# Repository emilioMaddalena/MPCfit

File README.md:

# MPCfit

Lightweight MPC approximations through tailored neural networks.

## Description :books:

We propose a particular feedforward neural network architecture to approximate model predictive controllers from data. The network features a quadratic program as one of its internal layers, employed to learn the MPC dual, as well as a final projection layer to guarantee feasibility of the control actions. It is shown that, given an appropriate network size, **any linear MPC controller can be learned**.

The so-called piecewise-affine neural network (PWA-NN) was used to learn an MPC controller for a buck dc-dc converter, and then embedded on an STM32 microcontroller. The control computations were carried out periodically in **less than 30 microseconds**. This repository contains all the files related to the project.

Evolution across epochs:

Final results:

## References :books:

```
@article{maddalena2021embedded,
  title={Embedded PWM predictive control of DC-DC power converters via piecewise-affine neural networks},
  author={Maddalena, E. T. and Specq, M. W. F. and Wisniewski, V. L. and Jones, C. N.},
  journal={IEEE Open Journal of the Industrial Electronics Society},
  volume={2},
  pages={199--206},
  year={2021},
  publisher={IEEE}
}
```
```
@article{maddalena2020neural,
  title={A neural network architecture to learn explicit MPC controllers from data},
  author={Maddalena, E. T. and Moraes, C. G. da S. and Waltrich, G. and Jones, C. N.},
  journal={IFAC-PapersOnLine},
  volume={53},
  number={2},
  pages={11362--11367},
  year={2020},
  publisher={Elsevier}
}
```

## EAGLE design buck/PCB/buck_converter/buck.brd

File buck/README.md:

## Buck converter 

A schemtic of the dc-dc converter: 

## Folders

:open_file_folder: Documents: PDF documents relevant to the project.

:open_file_folder: Firmware: C code for the STM32L4 microcontroller. The projects were developed in the STM32 CUBE-IDE and CUBE-MX environments.

:open_file_folder: PWA-NN: Contains the MATLAB scripts where the system model is defined and the MPC controller is designed and sampled. Also contain the python code used for defining and training the PWA-NN.

:open_file_folder: PCB: The schematic, layout and gerber files for the buck dc-dc converter printed circuit board. The design was carried out in Autodesk Eagle 9.5.

:open_file_folder: Scope: A set of oscilloscope screenshots obtained during operation (refer to the paper), and their associated .csv files.

:open_file_folder: Sketch: Illustration files for each of the figures present in the paper. Drawn in Sketch 68.2.

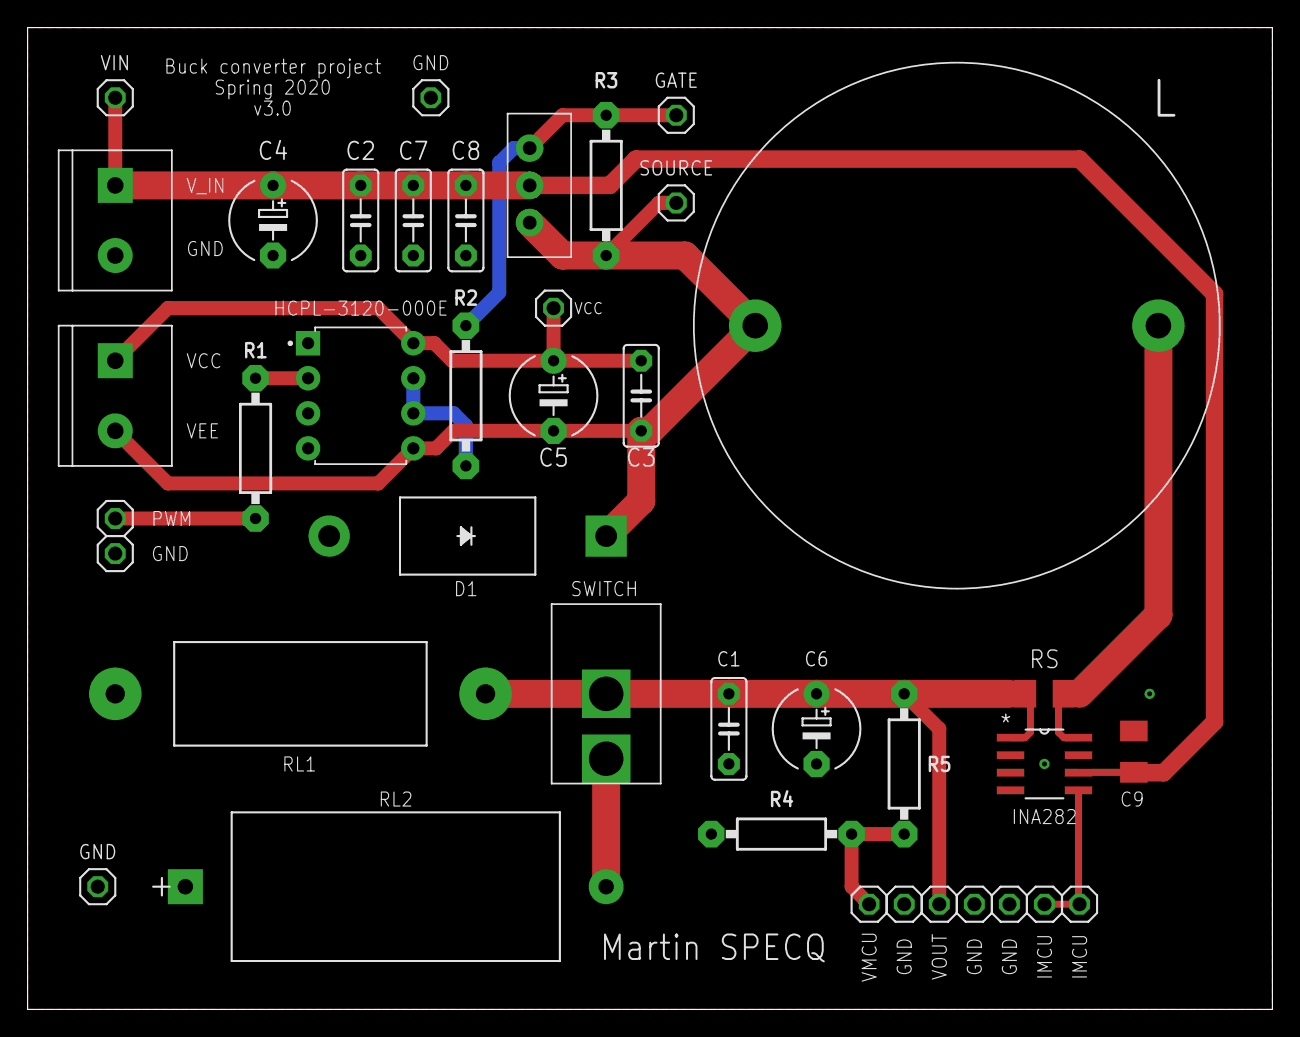
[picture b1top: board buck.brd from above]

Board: 2 copper layers, 90.2 x 71.1 mm, 40 parts (0 on the bottom side), 13 nets.

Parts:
C1, C2, C3: 100n; C5B2.5
C4, C5: 100u; E5-6
C6: 56u; E5-6
C7: 10n; C5B2.5
C8: 1n; C5B2.5
C9: 100n; C1206K
D1: DIODE_DO-201AD
GATE: 1X01
GDRVR: TE_282837-2
GND, GND2: 1X01
L: 10m; INDRD2921W163D3810H2616P
R1: 1k; 0207/10C
R2: 100; 0207/10C
R3: 10k; 0207/10C
R4: 22k; 0207/10C
R5: 56k; 0207/10C
R7, R9, R10, R11, R12, R13, R14, R15: 1X01
RL1: 100; RES_AC05
RL2: 100; YAG_SQP500
RS: 150m; M1206
SOURCE: 1X01
T: MOSFETMOSFET; MOSFET
U1: HCPL-3120-000E; DIP762W65P254L990H470Q8
U2: INA282AID; D8
U$1: ON_OFF
VCC: 1X01
VIN: 1X01
VMCU: 1X01
V_IN: TE_282837-2

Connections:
G: GATE.1, R2.2, R3.2, T.G
GND: C1.2, C2.2, C4.-, C6.-, C7.2, C8.2, C9.2, D1.2, GND.1, GND2.1, R4.1, R10.1, R11.1, R12.1, R13.1, RL1.1, RL2.1, U1.3, U2.2, U2.3, U2.7, V_IN.2
IMCU: R14.1, R15.1, U2.5
IND: L.2, RS.2, U2.8
unnamed: R2.1, U1.6, U1.7
unnamed: R1.2, U1.2
unnamed: RL2.2, U$1.P$2
PWM: R1.1, R9.1
VCC: C3.1, C5.+, GDRVR.1, U1.8, VCC.1
VEE: C3.2, C5.-, D1.1, GDRVR.2, L.1, R3.1, SOURCE.1, T.S, U1.5
VIN: C2.1, C4.+, C7.1, C8.1, C9.1, T.D, U2.6, VIN.1, V_IN.1
VMCU: R4.2, R5.1, VMCU.1
VOUT: C1.1, C6.+, R5.2, R7.1, RL1.2, RS.1, U2.1, U$1.P$1

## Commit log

2020-12-13 First update
2020-12-13 Picture update
2020-12-13 Update picture
2021-06-17 include all files
2021-06-17 create more readmes
2021-06-17 add buck diagram
2021-06-17 upload new documents
2021-06-17 update matlab scripts
2021-06-17 add gif
2021-06-17 relocate figs
2021-06-17 update python scripts
2021-06-17 organize python code and folder
2021-06-17 create new readme
2021-06-18 reorganize project
2021-06-18 add buck photo
2021-06-18 update python files
2021-06-18 rename folders
2021-06-18 clean pcb folder
2022-06-22 Bump numpy from 1.20.3 to 1.22.0 in /files/code/python
    Bumps [numpy](https://github.com/numpy/numpy) from 1.20.3 to 1.22.0.
    - [Release notes](https://github.com/numpy/numpy/releases)
    - [Changelog](https://github.com/numpy/numpy/blob/main/doc/HOWTO_RELEASE.rst)
    - [Commits](https://github.com/numpy/numpy/compare/v1.20.3...v1.22.0)
    ---
    updated-dependencies:
2023-07-06 Bump scipy from 1.6.3 to 1.10.0 in /files/code/python
    Bumps [scipy](https://github.com/scipy/scipy) from 1.6.3 to 1.10.0.
    - [Release notes](https://github.com/scipy/scipy/releases)
    - [Commits](https://github.com/scipy/scipy/compare/v1.6.3...v1.10.0)
    ---
    updated-dependencies:
    - dependency-name: scipy
